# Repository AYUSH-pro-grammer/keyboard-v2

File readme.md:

# Custom Mechanical Keyboard

## What is this?

A custom mechanical keyboard made with a custom PCB, individual locations for switches, a microcontroller and an I/O expander.

A small and custom keyboard with mechanical switches and keycaps.

## Why Build?

I wanted to build my own mechanical keyboard. This has allowed me to have a go at designing my own PCB, learning more about electronics, microcontrollers and how the keyboard circuits work.

I wanted to design my own PCB to get a full understanding of everything involved from the schematic to building it.

## Images

### 3D Keyboard Design

### PCB Layout

### Circuit Schematic

## Keyboard Matrix Testing

I created an Arduino test sketch for the Raspberry Pi Pico and MCP23017 to scan the full 85-key keyboard matrix. It detects key presses and releases and displays the assigned key names in the Serial Monitor at 115200 baud. The keymap can be edited to match the physical keyboard layout.

## How it was built

The keyboard is built around a custom designed PCB. The main controller is the Seeed XIAO nRF52840. There is also an MCP23017 I/O expander.

There are diodes in the keyboard matrix, resistors, capacitors, USB-C, battery connects. The keyboard also has mechanical switches fitted into the hotswap sockets.

## Components

Seeed XIAO nRF52840 – Main microcontroller

MCP23017 – I/O expander

Mechanical switches – Detects presses

Kailh Choc hotswap sockets – To fit switches into

Diodes – Part of keyboard matrix

Capacitors and Resistors – Other components

USB-C – USB connect

Battery – Connect to battery

## PCB Design

The PCB was designed in KiCad. I began by designing the schematic. From there I moved onto designing the PCB.

I added footprints for the switches, diodes, controller, I/O expander and other components.

## Assembly Instructions

Step 1 – Get PCB

Obtain your manufactured PCB. Check there are no obvious damages to the board. Ensure the component footprints and pads are clean.

Step 2 – Fit small components

Fit the diodes, resistors and capacitors. Ensure they are the right way round and the correct value.

Step 3 – Fit main components

Fit the MCP23017, USB C, battery and any other components needed. Ensure they are fitted according to the PCB.

Step 4 – Fit microcontroller

Fit the Seeed XIAO nRF52840 into its location. Ensure the pins are the right way round and connected correctly.

Step 5 – Fit hotswap sockets

Fit hotswap sockets to the PCB. Ensure they are fitted correctly.

Step 6 – Fit switches

Check the sockets are correct. Fit switches to the PCB. Ensure the pins are straight and fit into sockets.

Step 7 – Fit keycaps

Fit keycaps to the switches according to the keyboard layout.

## Bill of Materials (BOM)

| Component | Quantity | Price (USD) | Link |
|---|---:|---:|---|
| Raspberry Pi Pico | 1 | $4.48 | [Buy](https://www.dnatechindia.com/raspberry-pi-rpi-pico-buy-india.html) |
| 100nF Ceramic Disc Capacitor | 3 | $0.01 | [Buy](https://store.electrobot.co.in/product/104-pf) |
| 10µF 50V Ceramic Capacitor | 1 | $1.44 | [Buy](https://www.digikey.in/en/products/detail/tdk/FG26X5R1H106KRT06/5812039) |
| 1N4148 DO-35 Diodes | 84 (buy 100) | $0.74 | [Buy](https://tufonlinestore.com/product/1n4148-diode-10-pieces-pack/) |
| SS34 SMA Schottky Diodes | 2 | $0.03 | [Buy](https://bafnadevices.com/product/ss34-sma-40v-3a-schottky-diode-smd-package-do-214ac/) |
| 1×14 2.54mm Male Pin Header | 1 | $0.32 | [Buy](https://evelta.com/1x14-pin-2-54mm-pitch-male-square-pin/) |
| JST PH 2-Pin Right Angle Connector | 1 | $0.17 | [Buy](https://www.lioncircuits.com/parts/S2B-PH-K-S) |
| 4-Pin Boost Converter Header | 1 pack (5 pcs) | $0.73 | [Buy](https://robu.in/product/4-pin-female-11mm-tall-stackable-header-connector-for-arduino-5pcs/) |
| USB-C Receptacle GCT USB4105 | 1 | $1.03 | [Buy](https://www.lioncircuits.com/parts/usb4105-gf-a) |
| 5.1kΩ Resistors 1/4W | 2 (buy pack of 5) | $0.02 | [Buy](https://www.electronicscomp.com/5.1k-ohm-resistance) |
| 10kΩ Resistors 1/4W | 2 (buy pack of 10) | $0.16 | [Buy](https://www.theengineerstore.in/products/10k-ohm-resistor-1-4-watt-pack-of-10pcs) |
| 4.7kΩ Resistors 1/4W | 2 (buy pack of 5) | $0.02 | [Buy](https://www.electronicscomp.com/4.7k-ohm-resistance-1-4-watt) |
| Kailh Choc Hotswap Sockets | 85 (buy pack of 100) | $48.60 | [Buy](https://nilgiristores.in/product/100pieces-kailh-hot-swap-socket-for-low-profile-1350-chocolate-switches/) |
| Mechanical Keyboard Switches | 1 pack (100 pcs) | $10.54 | [Buy](https://www.amazon.in/NIHUIFDPY-Mechanical-Replacement-Dustproof-Keyswitches/dp/B0H4H4HHZW/) |
| ZORBES 130-Key Keycap Set | 1 pack | $10.54 | [Buy](https://www.amazon.in/ZORBES-130-Key-Topographic-Mechanical-Keyboard/dp/B0GZMBPHYB/) |
| MCP23017 DIP-28 I/O Expander | 1 | $2.79 | [Buy](https://www.chipmart.in/product/mcp23017-16-bit-input-output-expander-with-i2c-interface-ic-dip-28-package/) |
| Seeed XIAO nRF52840 | 1 | $12.11 | [Buy](https://findmychips.com/part/seeed-studio-xiao-nrf52840-ble-025947) |
| PCB Fabrication (JLCPCB) | 1 | $30.00 | [JLCPCB](https://jlcpcb.com) |

### Total Cost

**Components: $93.72**

**PCB Fabrication: $30.00**

**Grand Total: $123.72**

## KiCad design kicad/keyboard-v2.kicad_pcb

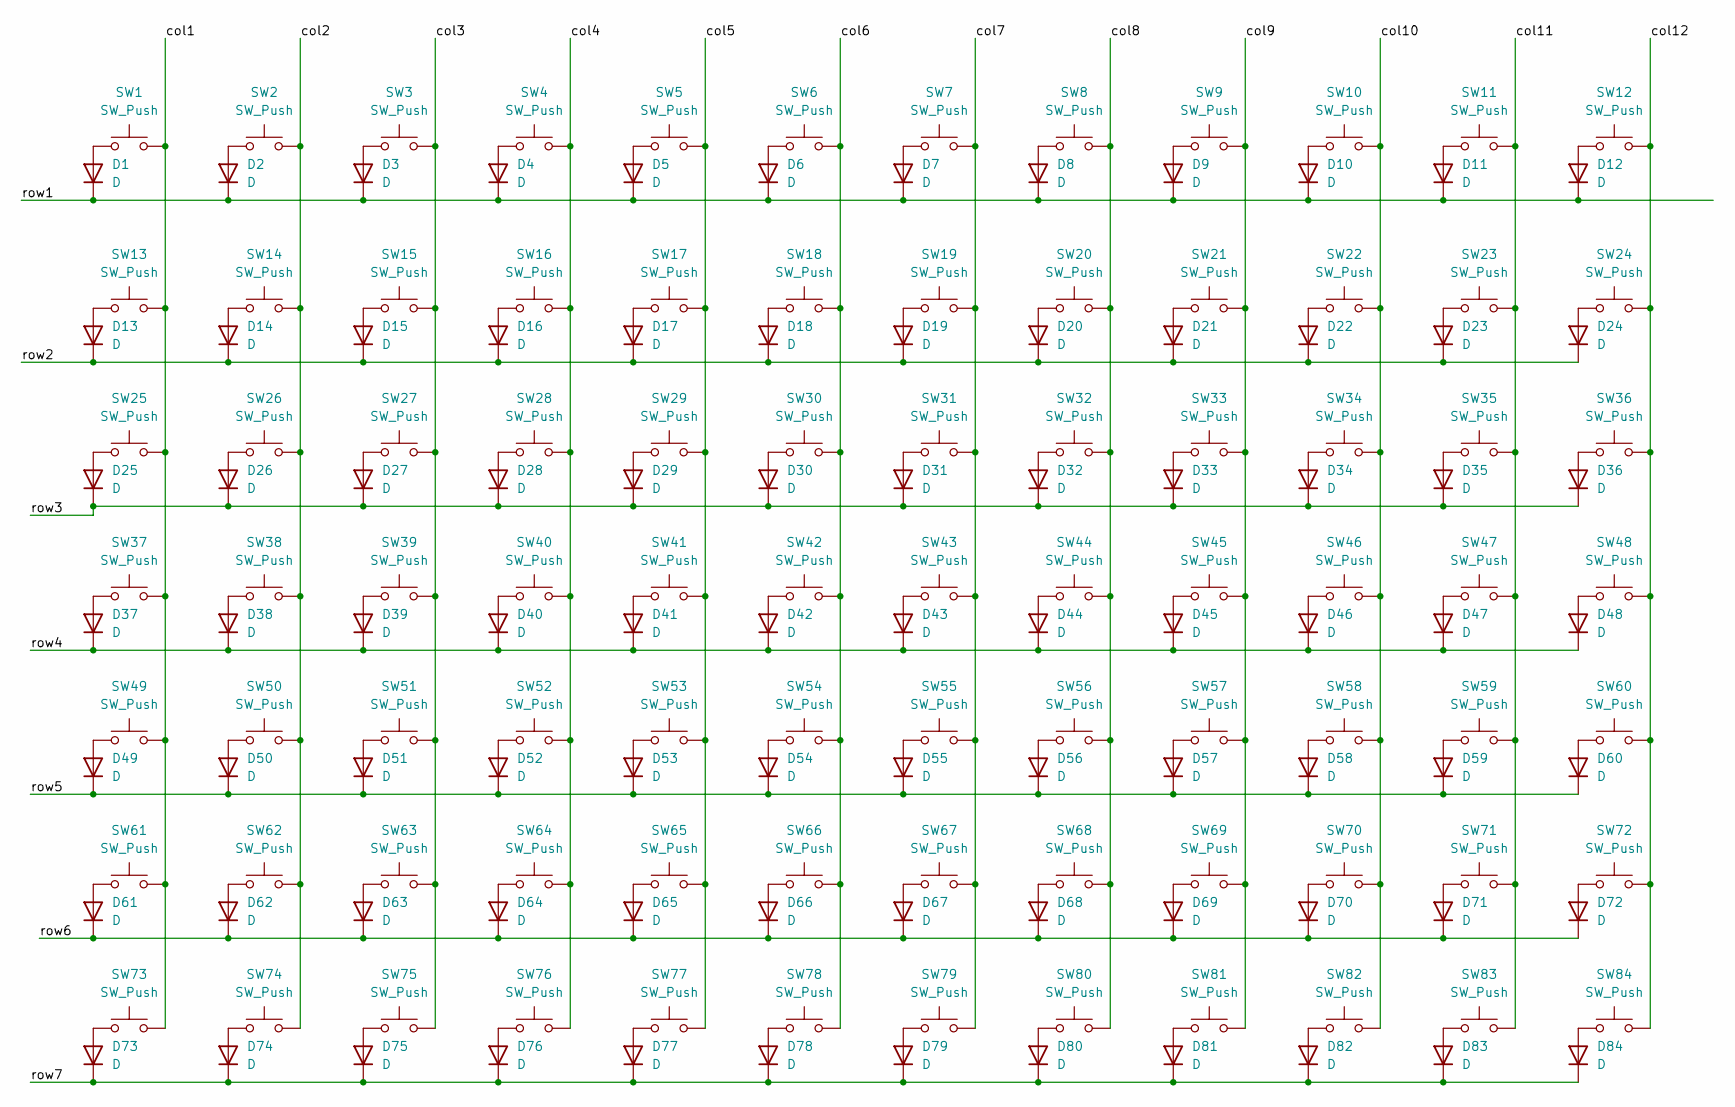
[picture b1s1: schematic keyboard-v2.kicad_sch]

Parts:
D1, D2, D3, D4, D5, D6, D7, D8, D9, D10, D11, D12, D13, D14, D15, D16, D17, D18, D19, D20, D21, D22, D23, D24, D25, D26, D27, D28, D29, D30, D31, D32, D33, D34, D35, D36, D37, D38, D39, D40, D41, D42, D43, D44, D45, D46, D47, D48, D49, D50, D51, D52, D53, D54, D55, D56, D57, D58, D59, D60, D61, D62, D63, D64, D65, D66, D67, D68, D69, D70, D71, D72, D73, D74, D75, D76, D77, D78, D79, D80, D81, D82, D83, D84: D; D_DO-35_SOD27_P10.16mm_Horizontal
SW1, SW2, SW3, SW4, SW5: SW_Push; SW_Hotswap_Kailh_Choc_V1V2_1.25u
SW6, SW7: SW_Push; SW_Hotswap_Kailh_Choc_V1V2_1.50u
SW8, SW9: SW_Push; SW_Hotswap_Kailh_Choc_V1V2_1.75u
SW10: SW_Push; SW_Hotswap_Kailh_Choc_V1V2_2.00u
SW11: SW_Push; SW_Hotswap_Kailh_Choc_V1V2_2.50u
SW12: SW_Push; SW_Hotswap_Kailh_Choc_V1V2_2.25u
SW13: SW_Push; SW_Hotswap_Kailh_Choc_V1V2_6.25u
SW14, SW15, SW16, SW17, SW18, SW19, SW20, SW21, SW22, SW23, SW24, SW25, SW26, SW27, SW28, SW29, SW30, SW31, SW32, SW33, SW34, SW35, SW36, SW37, SW38, SW39, SW40, SW41, SW42, SW43, SW44, SW45, SW46, SW47, SW48, SW49, SW50, SW51, SW52, SW53, SW54, SW55, SW56, SW57, SW58, SW59, SW60, SW61, SW62, SW63, SW64, SW65, SW66, SW67, SW68, SW69, SW70, SW71, SW72, SW73, SW74, SW75, SW76, SW77, SW78, SW79, SW80, SW81, SW82, SW83, SW84: SW_Push; SW_Hotswap_Kailh_Choc_V1V2_1.00u

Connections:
/Root/col1: SW1.2, SW13.2, SW25.2, SW37.2, SW49.2, SW61.2, SW73.2
/Root/col2: SW2.2, SW14.2, SW26.2, SW38.2, SW50.2, SW62.2, SW74.2
/Root/col3: SW3.2, SW15.2, SW27.2, SW39.2, SW51.2, SW63.2, SW75.2
/Root/col4: SW4.2, SW16.2, SW28.2, SW40.2, SW52.2, SW64.2, SW76.2
/Root/col5: SW5.2, SW17.2, SW29.2, SW41.2, SW53.2, SW65.2, SW77.2
/Root/col6: SW6.2, SW18.2, SW30.2, SW42.2, SW54.2, SW66.2, SW78.2
/Root/col7: SW7.2, SW19.2, SW31.2, SW43.2, SW55.2, SW67.2, SW79.2
/Root/col8: SW8.2, SW20.2, SW32.2, SW44.2, SW56.2, SW68.2, SW80.2
/Root/col9: SW9.2, SW21.2, SW33.2, SW45.2, SW57.2, SW69.2, SW81.2
/Root/col10: SW10.2, SW22.2, SW34.2, SW46.2, SW58.2, SW70.2, SW82.2
/Root/col11: SW11.2, SW23.2, SW35.2, SW47.2, SW59.2, SW71.2, SW83.2
/Root/col12: SW12.2, SW24.2, SW36.2, SW48.2, SW60.2, SW72.2, SW84.2
/Root/row1: D1.1 (K), D2.1 (K), D3.1 (K), D4.1 (K), D5.1 (K), D6.1 (K), D7.1 (K), D8.1 (K), D9.1 (K), D10.1 (K), D11.1 (K), D12.1 (K)
/Root/row2: D13.1 (K), D14.1 (K), D15.1 (K), D16.1 (K), D17.1 (K), D18.1 (K), D19.1 (K), D20.1 (K), D21.1 (K), D22.1 (K), D23.1 (K), D24.1 (K)
/Root/row3: D25.1 (K), D26.1 (K), D27.1 (K), D28.1 (K), D29.1 (K), D30.1 (K), D31.1 (K), D32.1 (K), D33.1 (K), D34.1 (K), D35.1 (K), D36.1 (K)
/Root/row4: D37.1 (K), D38.1 (K), D39.1 (K), D40.1 (K), D41.1 (K), D42.1 (K), D43.1 (K), D44.1 (K), D45.1 (K), D46.1 (K), D47.1 (K), D48.1 (K)
/Root/row5: D49.1 (K), D50.1 (K), D51.1 (K), D52.1 (K), D53.1 (K), D54.1 (K), D55.1 (K), D56.1 (K), D57.1 (K), D58.1 (K), D59.1 (K), D60.1 (K)
/Root/row6: D61.1 (K), D62.1 (K), D63.1 (K), D64.1 (K), D65.1 (K), D66.1 (K), D67.1 (K), D68.1 (K), D69.1 (K), D70.1 (K), D71.1 (K), D72.1 (K)
/Root/row7: D73.1 (K), D74.1 (K), D75.1 (K), D76.1 (K), D77.1 (K), D78.1 (K), D79.1 (K), D80.1 (K), D81.1 (K), D82.1 (K), D83.1 (K), D84.1 (K)
unnamed: D1.2 (A), SW1.1
unnamed: D2.2 (A), SW2.1
unnamed: D3.2 (A), SW3.1
unnamed: D4.2 (A), SW4.1
unnamed: D5.2 (A), SW5.1
unnamed: D6.2 (A), SW6.1
unnamed: D7.2 (A), SW7.1
unnamed: D8.2 (A), SW8.1
unnamed: D9.2 (A), SW9.1
unnamed: D10.2 (A), SW10.1
unnamed: D11.2 (A), SW11.1
unnamed: D12.2 (A), SW12.1
unnamed: D13.2 (A), SW13.1
unnamed: D14.2 (A), SW14.1
unnamed: D15.2 (A), SW15.1
unnamed: D16.2 (A), SW16.1
unnamed: D17.2 (A), SW17.1
unnamed: D18.2 (A), SW18.1
unnamed: D19.2 (A), SW19.1
unnamed: D20.2 (A), SW20.1
unnamed: D21.2 (A), SW21.1
unnamed: D22.2 (A), SW22.1
unnamed: D23.2 (A), SW23.1
unnamed: D24.2 (A), SW24.1
unnamed: D25.2 (A), SW25.1
unnamed: D26.2 (A), SW26.1
unnamed: D27.2 (A), SW27.1
unnamed: D28.2 (A), SW28.1
unnamed: D29.2 (A), SW29.1
unnamed: D30.2 (A), SW30.1
unnamed: D31.2 (A), SW31.1
unnamed: D32.2 (A), SW32.1
unnamed: D33.2 (A), SW33.1
unnamed: D34.2 (A), SW34.1
unnamed: D35.2 (A), SW35.1
unnamed: D36.2 (A), SW36.1
unnamed: D37.2 (A), SW37.1
unnamed: D38.2 (A), SW38.1
unnamed: D39.2 (A), SW39.1
unnamed: D40.2 (A), SW40.1
unnamed: D41.2 (A), SW41.1
unnamed: D42.2 (A), SW42.1
unnamed: D43.2 (A), SW43.1
unnamed: D44.2 (A), SW44.1
unnamed: D45.2 (A), SW45.1
unnamed: D46.2 (A), SW46.1
unnamed: D47.2 (A), SW47.1
unnamed: D48.2 (A), SW48.1
unnamed: D49.2 (A), SW49.1
unnamed: D50.2 (A), SW50.1
unnamed: D51.2 (A), SW51.1
unnamed: D52.2 (A), SW52.1
unnamed: D53.2 (A), SW53.1
unnamed: D54.2 (A), SW54.1
unnamed: D55.2 (A), SW55.1
unnamed: D56.2 (A), SW56.1
unnamed: D57.2 (A), SW57.1
unnamed: D58.2 (A), SW58.1
unnamed: D59.2 (A), SW59.1
unnamed: D60.2 (A), SW60.1
unnamed: D61.2 (A), SW61.1
unnamed: D62.2 (A), SW62.1
unnamed: D63.2 (A), SW63.1
unnamed: D64.2 (A), SW64.1
unnamed: D65.2 (A), SW65.1
unnamed: D66.2 (A), SW66.1
unnamed: D67.2 (A), SW67.1
unnamed: D68.2 (A), SW68.1
unnamed: D69.2 (A), SW69.1
unnamed: D70.2 (A), SW70.1
unnamed: D71.2 (A), SW71.1
unnamed: D72.2 (A), SW72.1
unnamed: D73.2 (A), SW73.1
unnamed: D74.2 (A), SW74.1
unnamed: D75.2 (A), SW75.1
unnamed: D76.2 (A), SW76.1
unnamed: D77.2 (A), SW77.1
unnamed: D78.2 (A), SW78.1
unnamed: D79.2 (A), SW79.1
unnamed: D80.2 (A), SW80.1
unnamed: D81.2 (A), SW81.1
unnamed: D82.2 (A), SW82.1
unnamed: D83.2 (A), SW83.1
unnamed: D84.2 (A), SW84.1

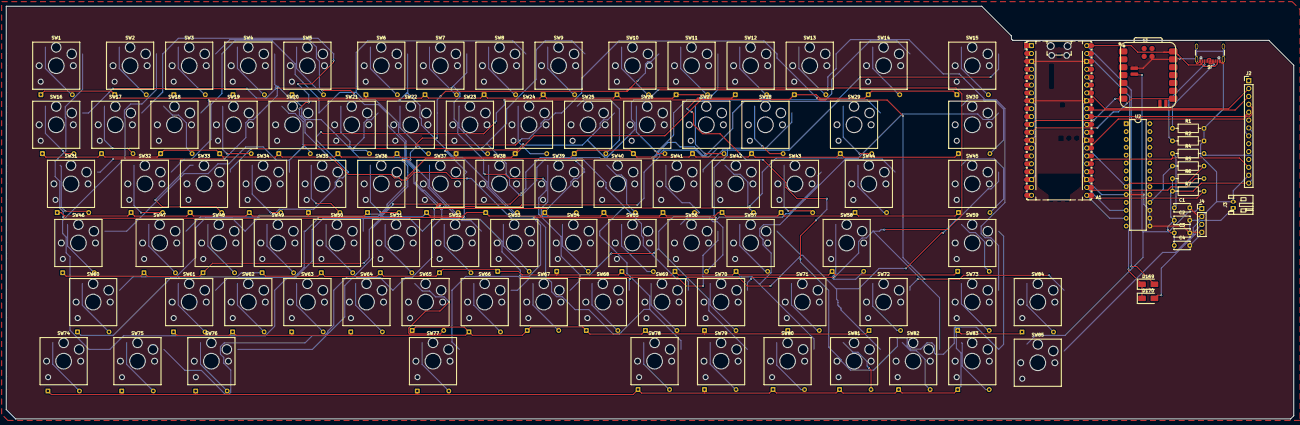
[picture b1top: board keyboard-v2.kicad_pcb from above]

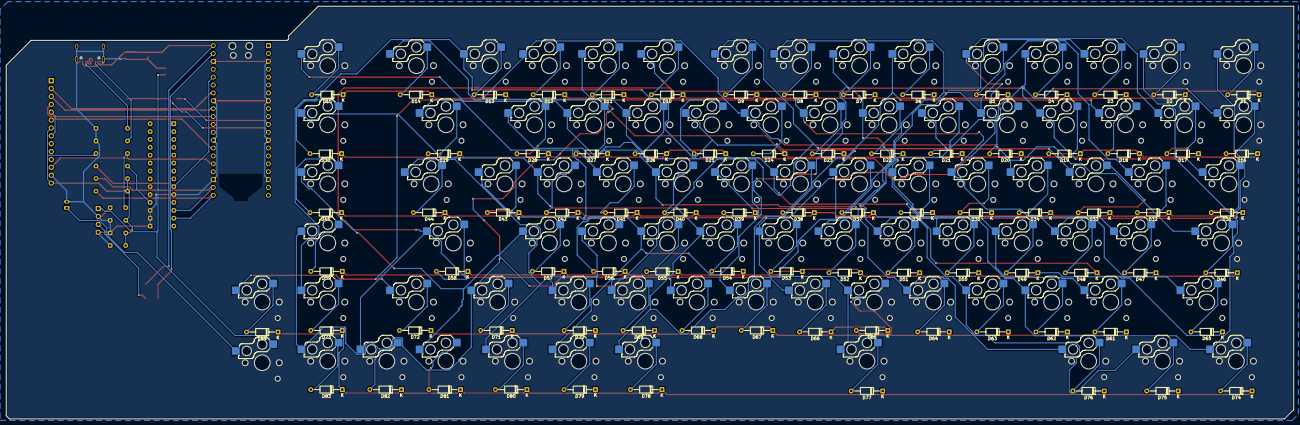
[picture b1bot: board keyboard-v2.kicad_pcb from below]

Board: 2 copper layers, 415.0 x 133.0 mm, 188 parts (84 on the bottom side), 125 nets.

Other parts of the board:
A1: RaspberryPi_Pico; RaspberryPi_Pico_Common_Unspecified
C1: 100nf; C_Disc_D5.0mm_W2.5mm_P5.00mm
C2, C3: 100nF; C_Disc_D5.0mm_W2.5mm_P5.00mm
C4: 10µF; C_Disc_D5.0mm_W2.5mm_P5.00mm
D169, D170: SS34; D_SMA
J2: Conn_01x14; PinHeader_1x14_P2.54mm_Vertical
J3: battery; JST_PH_S2B-PH-K_1x02_P2.00mm_Horizontal
J4: Boost Convertor; PinHeader_1x04_P2.54mm_Vertical
J5: USB_C_Receptacle_USB2.0_16P; USB_C_Receptacle_GCT_USB4105-xx-A_16P_TopMnt_Horizontal
R1, R2: 5.1k; R_Axial_DIN0207_L6.3mm_D2.5mm_P10.16mm_Horizontal
R4: 10k; R_Axial_DIN0207_L6.3mm_D2.5mm_P10.16mm_Horizontal
R5: 10kohm; R_Axial_DIN0207_L6.3mm_D2.5mm_P10.16mm_Horizontal
R6, R7: 4.7kΩ; R_Axial_DIN0207_L6.3mm_D2.5mm_P10.16mm_Horizontal
SW85: SW_SPST; SW_Hotswap_Kailh_Choc_V1V2_1.00u
U2: MCP23017x-x-SP; DIP-28_W7.62mm
U3: XIAO-nRF52840-SMD

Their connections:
+3V3: C2.1, C3.1, C4.1, J2.7, J2.14, R4.2, R6.1, R7.1
/led/BAT+: J3.1, SW85.2 (B)
/led/BC_VIN+: J4.1, SW85.1 (A), U3.19 (VBAT)
/led/BC_VOUT+: D170.2 (A), J4.3
/led/PICO_TX_XIAO_RX: A1.11 (GPIO8), U3.7 (D6)
/led/SYSTEM_5V: A1.39 (VSYS), D169.1 (K), D170.1 (K)
/led/TFT_CS: A1.25 (GPIO19), C1.1, J2.12, R4.1
/led/TFT_MISO: A1.34 (GPIO28_ADC2), J2.2
/led/TFT_MOSI: A1.32 (GPIO27_ADC1), J2.3
/led/TFT_SCK: A1.31 (GPIO26_ADC0), J2.5, J2.8
/led/T_CS: A1.27 (GPIO21), J2.4
/led/USB_5V: A1.40 (VBUS), D169.2 (A), J5.A4 (VBUS), J5.A9 (VBUS), J5.B4 (VBUS), J5.B9 (VBUS), U3.14 (VBUS)
/led/XIAO_TX_PICO_RX: A1.12 (GPIO9), U3.8 (D7)
/led/sck_mcp: A1.22 (GPIO17), R6.2, U2.12 (SCK)
/led/sda_mcp: A1.21 (GPIO16), R7.2, U2.13 (SDA)
/led/usb_d+: J5.A6 (D+), J5.B6 (D+)
/led/usb_d-: J5.A7 (D-), J5.B7 (D-)
GND: A1.3 (GND), A1.8 (GND), A1.13 (GND), A1.18 (GND), A1.23 (GND), A1.28 (GND), A1.33 (AGND), A1.38 (GND), C1.2, C2.2, C3.2, C4.2, J2.13, J3.2, J4.2, J4.4, J5.A1 (GND), J5.A12 (GND), J5.B1 (GND), J5.B12 (GND), J5.SH (SHIELD), R1.2, R2.2, U2.10 (V_{SS}), U2.15 (A0), U2.16 (A1), U2.17 (A2), U3.13 (GND), U3.18 (GND), U3.20 (GND)
unnamed: A1.36 (3V3), R5.2, U2.9 (V_{DD})
unnamed: J5.A5 (CC1), R1.1
unnamed: J5.B5 (CC2), R2.1
unnamed: R5.1, U2.18 (~RESET)
